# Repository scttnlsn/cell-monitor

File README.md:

# cell-monitor

Battery cell monitor and balancer based on the AVR ATTiny85 MCU.

* reads cell voltage
* switches balancing FET
* communicates with a host controller via isolated serial
* low power consumption (<1mA when idle, ~2mA while active)

A cell monitor is intended to monitor a single cell as part of a larger series pack.
The cell monitor is powered directly from the cell it monitors and works with any chemistry
where the voltage remains within 1.8V-5.5V (i.e. lithium-ion, LiFePO4).

## Build

Dependencies:

* [pio](http://platformio.org)
* [make](https://www.gnu.org/software/make/)

```
make
make fuse
make flash
```

## Wiring

Cell monitors are wired in a daisy chain with the TX from the host controller connected to
the RX of cell monitor 1, the TX of cell monitor 1 connected to the RX of cell monitor 2, etc.
The TX of cell monitor N is connected to the RX of the host controller.

```
+-----------+
| HOST   RX | <------------------------------------------+
|        TX | >---+    +--->---+    +--->  ...  >---+    |
+-----------+     |    |       |    |               |    |
                  |    |       |    |               |    |
                +--------+   +--------+           +--------+
                | RX  TX |   | RX  TX |    ...    | RX  TX |
                |    1   |   |    2   |    ...    |    N   |
                +--------+   +--------+    ...    +--------+
```

Cell monitors are addressed by their position in the daisy chain.

## Serial protocol

The host controller initiates all communication with the network of cell monitors and does so at 9600 baud.
The host controller sends a request packet which is forwarded through the daisy chain to an addressed cell
monitor.  The addressed cell monitor will reply with a similar response packet which will be forwarded through
the remaining chain and eventually read by the host controller.

#### Packet structure

Communication consists of 5 byte packets with the following structure:

| Byte  | 7     | 6     | 5     |    4  |    3  |    2  |    1  |     0 |
| ----- | ----- | ----- | ----- | ----- | ----- | ----- | ----- | ----- |
| **1** | ID7   | ID6   | ID5   | ID4   | ID3   | ID2   | ID1   | ID0   |
| **1** | ADDR6 | ADDR5 | ADDR4 | ADDR3 | ADDR2 | ADDR1 | ADDR0 | REQ   |
| **2** | REG6  | REG5  | REG4  | REG3  | REG2  | REG1  | REG0  | WRITE |
| **3** | VAL15 | VAL14 | VAL13 | VAL12 | VAL11 | VAL10 | VAL9  | VAL8  |
| **4** | VAL7  | VAL6  | VAL5  | VAL4  | VAL3  | VAL2  | VAL1  | VAL0  |
| **5** | CRC7  | CRC6  | CRC5  | CRC4  | CRC3  | CRC2  | CRC1  | CRC0  |

* **ID** - packet ID
* **ADDR6-0** - cell monitor address
* **REQ** - 1 if packet is a request, 0 if packet is a response
* **REG6-0** - register (described below)
* **WRITE** - 1 if packet is a write command, 0 if packet is a read command
* **VAL15-0** - value
* **CRC7-0** - CRC8 of prior 4 bytes

#### Registers

* `0x1` - cell address (1 byte, unsigned)
* `0x2` - cell voltage (2 bytes, unsigned)
* `0x3` - balance (1 if balancing, 0 otherwise)

#### Example

*Reading the voltage from cell 1*

Request:

| Byte | Value    |
| ---- | -------- |
| 1    | 00000001 |
| 2    | 00000011 |
| 3    | 00000110 |
| 4    | 00000000 |
| 5    | 00000000 |
| 6    | 00100101 |

* `ID` = 1
* `ADDR` = 1
* `REQ` bit set to 1
* `REG` = 3
* `WRITE` bit set to 0
* `VAL` is not applicable for read request
* `CRC` = crc8(4345692160)

The following response will be received:

| Byte | Value    |
| ---- | -------- |
| 1    | 00000001 |
| 1    | 00000010 |
| 2    | 00000110 |
| 3    | 00001100 |
| 4    | 11100100 |
| 5    | 01111101 |

* `ID` = 1
* `ADDR` = 1
* `REQ` bit set to 0
* `REG` = 3
* `WRITE` bit set to 0
* `VAL` is the returned voltage (3300mV in this example)
* `CRC` = crc8(4328918244)

#### Address assignment

A cell monitor has an undefined address when it is initially powered on.  The host controller
needs to initiate an address assignment request (which has slightly different semantics than
other value requests):

| Byte | Value    |
| ---- | -------- |
| 1    | 00000001 |
| 2    | 00000001 |
| 3    | 00000011 |
| 4    | 00000000 |
| 5    | 00000001 |
| 6    | 11001110 |

* `ID` = 1
* `ADDR` = 0 (broadcast to all cell monitors)
* `REQ` bit set to 1
* `REG` = 1
* `WRITE` bit set to 1
* `VAL` = first cell address
* `CRC` = crc8(4311941121)

The first cell monitor will receive the request and set its address to the value in the `VAL` field.
Instead of sending a response it will increment the `VAL` field and forward the request onward.
Eventually the host controller will receive the same request packet (with an incremented `VAL`).
The host controller should assert that `VAL` equals 1 more than the number of cell monitors in the
network.

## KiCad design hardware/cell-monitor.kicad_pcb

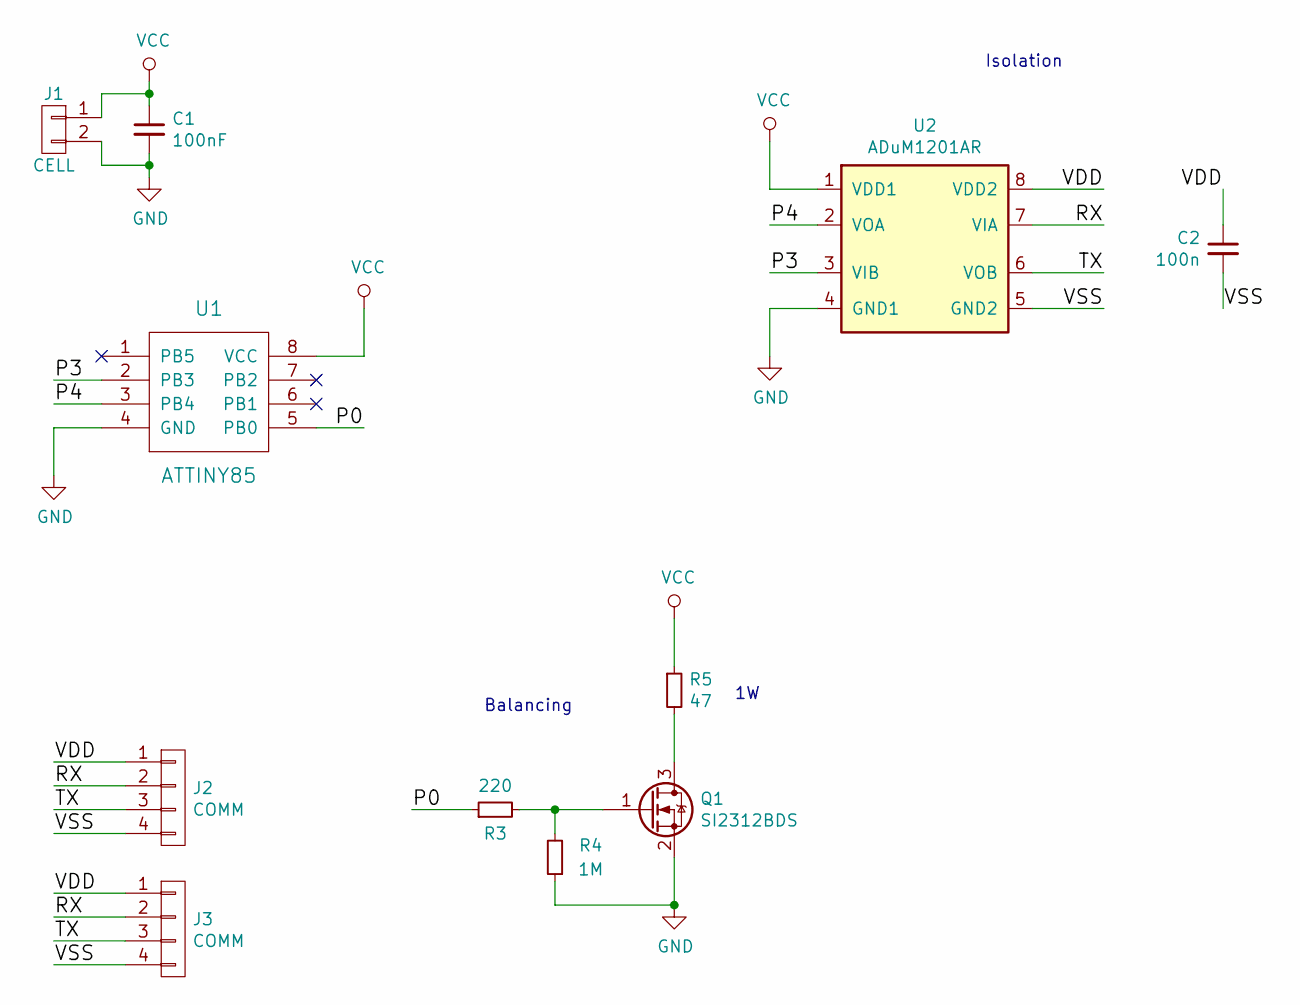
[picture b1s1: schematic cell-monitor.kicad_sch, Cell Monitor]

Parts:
C1: 100nF; C_1206_HandSoldering
C2: 100n; C_1206_HandSoldering
J1: CELL; bornier2
J2, J3: COMM; Pin_Header_Straight_1x04_Pitch2.54mm
Q1: SI2312BDS; SOT-23
R3: 220; R_1206_HandSoldering
R4: 1M; R_1206_HandSoldering
R5: 47; R_2512_HandSoldering
U1: ATTINY85; DIP-8_W7.62mm_Socket
U2: ADuM1201AR; SOIC-8_3.9x4.9mm_Pitch1.27mm

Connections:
/P0: R3.1, U1.5 (PB0)
/P3: U1.2 (PB3), U2.3 (VIB)
/P4: U1.3 (PB4), U2.2 (VOA)
/RX: J2.2, J3.2, U2.7 (VIA)
/TX: J2.3, J3.3, U2.6 (VOB)
/VDD: C2.1, J2.1, J3.1, U2.8 (VDD2)
/VSS: C2.2, J2.4, J3.4, U2.5 (GND2)
GND: C1.2, J1.2, Q1.2 (S), R4.1, U1.4 (GND), U2.4 (GND1)
unnamed: Q1.3 (D), R5.2
unnamed: Q1.1 (G), R3.2, R4.2
VCC: C1.1, J1.1, R5.1, U1.8 (VCC), U2.1 (VDD1)

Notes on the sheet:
Isolation
Balancing

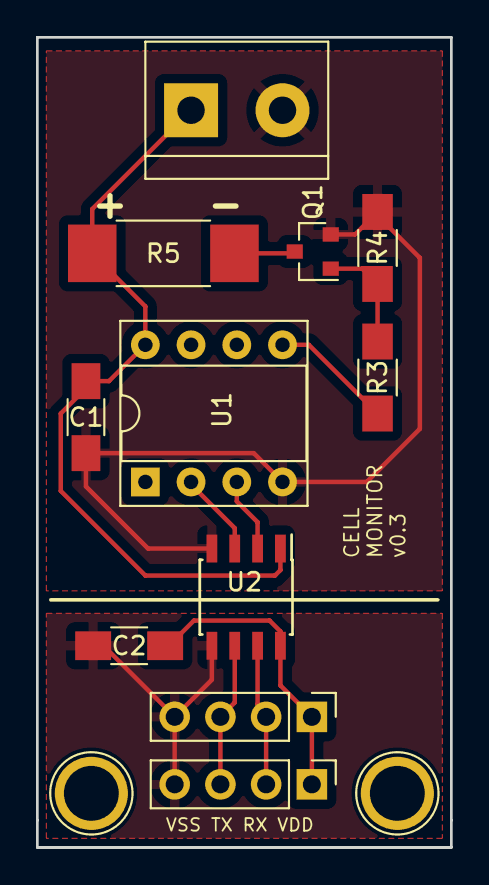
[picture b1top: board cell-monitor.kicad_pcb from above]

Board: 2 copper layers, 23.0 x 45.0 mm, 11 parts (0 on the bottom side), 11 nets.

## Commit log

2017-08-08 Added basic cell balancing enable command
2017-08-08 Added reset watchdog
2017-08-08 Added balancing autodisable after time interval
2017-08-08 Consolidate command scripts
2017-08-15 Sleep after handling command
2017-08-15 More generic command client
2017-08-15 Use a noninverting digital isolator
2017-08-15 Make cell address and ref voltage configurable via env var
2017-08-15 Added README
2017-08-15 Cleanup, extract various classes
2017-08-15 Added LICENSE
2017-08-15 Added schematic
2017-08-18 Added thermistor for cell temp monitoring
2017-08-18 Update schematic
2017-08-18 Added series gate resistor
2017-11-28 Added ADUM1250-based schematic and PCB layout
2017-12-07 Added I2C communication, nonblocking ADC
2018-03-07 Added KiCad project with hardware schematic and PCB layout
2018-03-21 Fix description of command script
2018-05-21 Initial work on new, daisy chained protocol
2018-06-09 Voltage calibration
2018-06-09 Rename client script
2018-06-09 Added serial protocol info to README
2018-06-09 Updated README with address assignment info
2018-06-14 Remove voltage calibration for now
2018-06-14 Fix typo in README
2018-09-10 Added avr/eeprom.h include
2018-09-25 Remove sleep from Python client
2025-05-16 Protocol update
    - remove temperature check (pack monitor can do this)
    - add `id` byte to packet
    - remove irrelevant registers
2025-05-23 Remove temp related hardware
2025-05-23 Clean up KiCad files
